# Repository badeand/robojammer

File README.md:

# robojammer

- [Video 1](https://youtu.be/M-0gTvquCPc)
- [Video 2](https://youtu.be/tEY_5-jrM3s)
- [Video 3 (feb 2023)](https://youtube.com/shorts/mlRzYQ1tYXU?feature=share)

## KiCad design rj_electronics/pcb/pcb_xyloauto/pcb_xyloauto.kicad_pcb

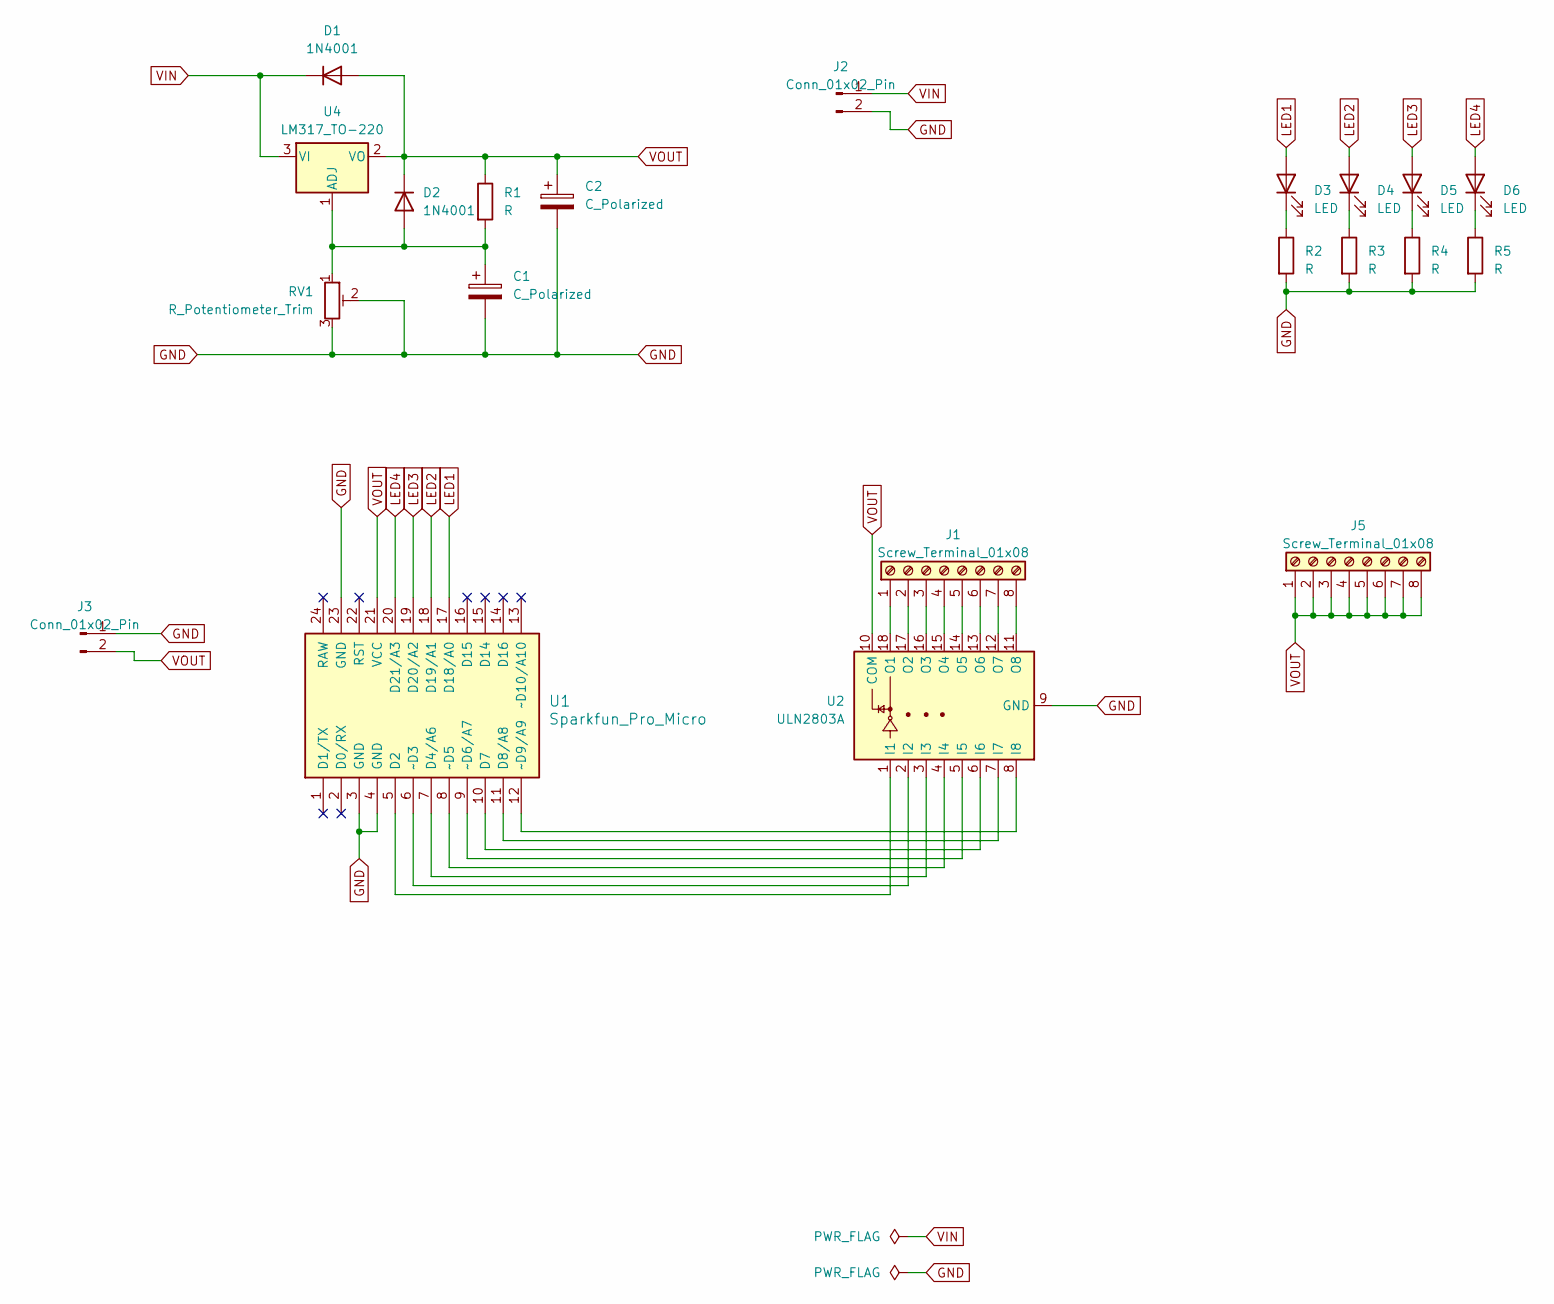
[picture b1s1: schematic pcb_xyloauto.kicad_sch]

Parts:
C1: C_Polarized; CP_Radial_D7.5mm_P2.50mm
C2: C_Polarized; CP_Radial_D10.0mm_P2.50mm
D1, D2: 1N4001; D_DO-41_SOD81_P10.16mm_Horizontal
D3, D4, D5, D6: LED; LED_D5.0mm
J1, J5: Screw_Terminal_01x08; TerminalBlock_Phoenix_PT-1,5-8-3.5-H_1x08_P3.50mm_Horizontal
J2, J3: Conn_01x02_Pin; PinHeader_1x02_P2.54mm_Vertical
R1, R2, R3, R4, R5: R; R_Axial_DIN0207_L6.3mm_D2.5mm_P10.16mm_Horizontal
RV1: R_Potentiometer_Trim; Potentiometer_Bourns_3299W_Vertical
U1: Sparkfun_Pro_Micro
U2: ULN2803A; DIP-18_W7.62mm_Socket
U4: LM317_TO-220; TO-220-3_Vertical

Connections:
GND: C1.2, C2.2, J2.2, J3.1, R2.2, R3.2, R4.2, R5.2, RV1.2, RV1.3, U1.3 (GND), U1.4 (GND), U1.23 (GND), U2.9 (GND)
LED1: D3.2 (A), U1.17 (D18/A0)
LED2: D4.2 (A), U1.18 (D19/A1)
LED3: D5.2 (A), U1.19 (D20/A2)
LED4: D6.2 (A), U1.20 (D21/A3)
unnamed: C1.1, D2.2 (A), R1.2, RV1.1, U4.1 (ADJ)
unnamed: D3.1 (K), R2.1
unnamed: D4.1 (K), R3.1
unnamed: D5.1 (K), R4.1
unnamed: D6.1 (K), R5.1
unnamed: J1.1, U2.18 (O1)
unnamed: J1.2, U2.17 (O2)
unnamed: J1.3, U2.16 (O3)
unnamed: J1.4, U2.15 (O4)
unnamed: J1.5, U2.14 (O5)
unnamed: J1.6, U2.13 (O6)
unnamed: J1.7, U2.12 (O7)
unnamed: J1.8, U2.11 (O8)
unnamed: U1.5 (D2), U2.1 (I1)
unnamed: U1.7 (D4/A6), U2.3 (I3)
unnamed: U1.10 (D7), U2.6 (I6)
unnamed: U1.11 (D8/A8), U2.7 (I7)
unnamed: U1.6 (~D3), U2.2 (I2)
unnamed: U1.8 (~D5), U2.4 (I4)
unnamed: U1.9 (~D6/A7), U2.5 (I5)
unnamed: U1.12 (~D9/A9), U2.8 (I8)
VIN: D1.1 (K), J2.1, U4.3 (VI)
VOUT: C2.1, D1.2 (A), D2.1 (K), J3.2, J5.1, J5.2, J5.3, J5.4, J5.5, J5.6, J5.7, J5.8, R1.1, U1.21 (VCC), U2.10 (COM), U4.2 (VO)

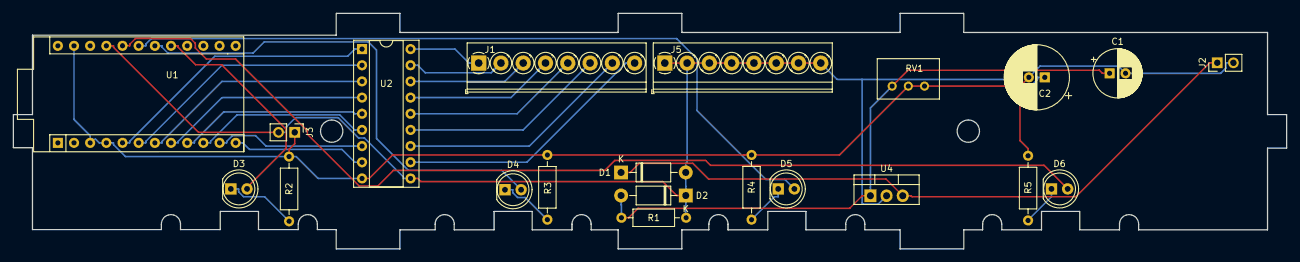
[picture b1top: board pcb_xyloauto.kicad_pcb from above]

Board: 2 copper layers, 200.0 x 37.0 mm, 21 parts (0 on the bottom side), 28 nets.

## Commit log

2022-04-06 initial
2022-04-08 solenoid holder
2022-04-11 more notes
2022-04-30 drawings
2022-07-04 new draing
2022-07-04 sketch done
2022-07-04 bottom plate
2022-07-04 array walls
2022-07-04 top fungerer
2022-07-04 top screws
2022-07-04 screws bottom
2022-07-04 topbottom complete
2022-07-04 reomved filletts
2022-07-06 WIP fingers
2022-07-06 bottom fingers
2022-07-06 divider holes
2022-07-06 refined
2022-07-06 fillets and prints
2022-07-06 export
2022-10-13 ignore
2022-10-20 ledninger
2023-01-08 removed bodies
2023-01-08 bottom OK
2023-02-14 roll over notes
2023-02-14 screws
2023-02-14 laser cuts
2023-02-17 redimentary velocivty
2023-02-17 cleanup
2023-02-24 imagrs
2023-03-22 renaming
2023-03-22 xylophonerobot_v4
2024-02-10 LED holes
